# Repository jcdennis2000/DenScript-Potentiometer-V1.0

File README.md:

# DenScript-Potentiometer-V1.0

The DenScript Potentiometer is a 10K potentiometer housed in a convenient package that allows it to be easily attached to projects, with our DenScript colour coded headers to make wiring far easier! Simply connect the RED pin to positive voltage (VCC), the BLACK pin to negative voltage (GND) and the GREEN pin to an input pin on your micro controller or development board!

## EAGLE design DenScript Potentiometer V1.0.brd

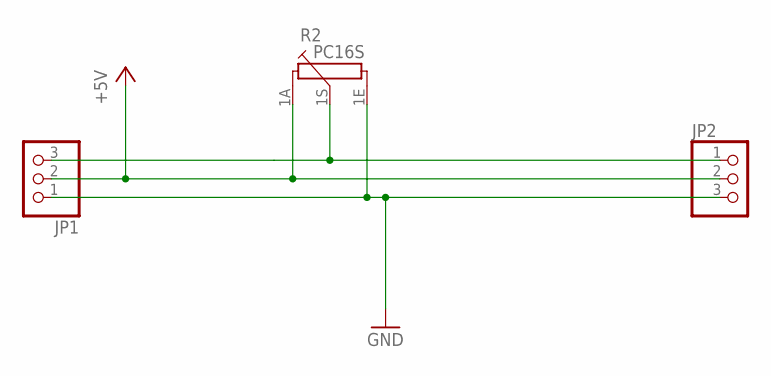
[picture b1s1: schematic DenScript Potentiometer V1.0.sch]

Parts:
JP1, JP2: PINHD-1X3; 1X03
R2: PC16S

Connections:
+5V: JP1.2, JP2.2, R2.1A
GND: JP1.1, JP2.3, R2.1E
unnamed: JP1.3, JP2.1, R2.1S

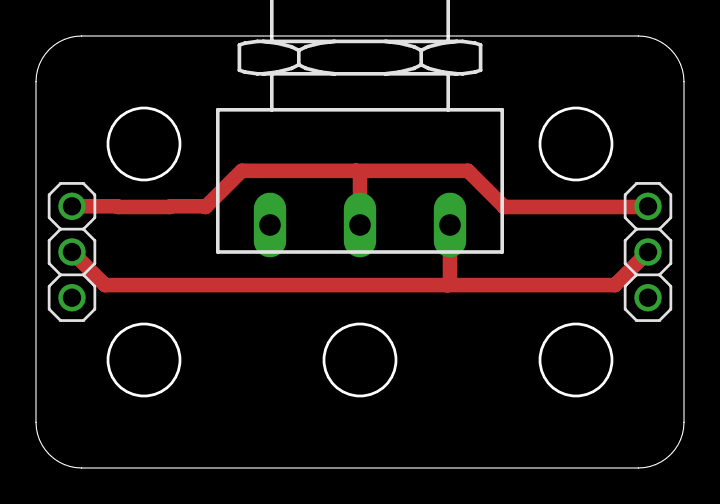
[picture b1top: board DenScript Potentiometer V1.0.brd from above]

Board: 2 copper layers, 35.8 x 23.8 mm, 3 parts (0 on the bottom side), 3 nets.

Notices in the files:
DenScript Potentiometer V1.0.brd:
Dennistries Ltd (c) 2019
